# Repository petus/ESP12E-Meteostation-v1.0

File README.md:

# ESP12E-Meteostation-v1.0<br>
Meteostation with ESP12E (NodeMCU) and Si7021 (temperature and humidity sensor)<br>
<br>
PCB is designed in eagle<br>
The platic box is KM-27<br>
<br>
FLASHING: <br>
 1.) Choose NodeMCU v1.0 (ESP12E Module) in Tools -> Board<br>
for NodeMCU board:<br>
 2.) Upload the code<br>
for PCB with ESP12E:<br>
 2.) Press the Reset button and Flash button together and hold it<br>
 3.) Click to Upload the code in Arduino IDE<br>
 4.) In the moment when the console shows <strong>Uploading</strong> leave the Reset button, then the code will be uploaded<br>
<br>
websites: <br>
CZ http://chiptron.petus.cz/articles.php?article_id=93 <br>
EN http://time4ee.com/articles.php?article_id=33 <br>

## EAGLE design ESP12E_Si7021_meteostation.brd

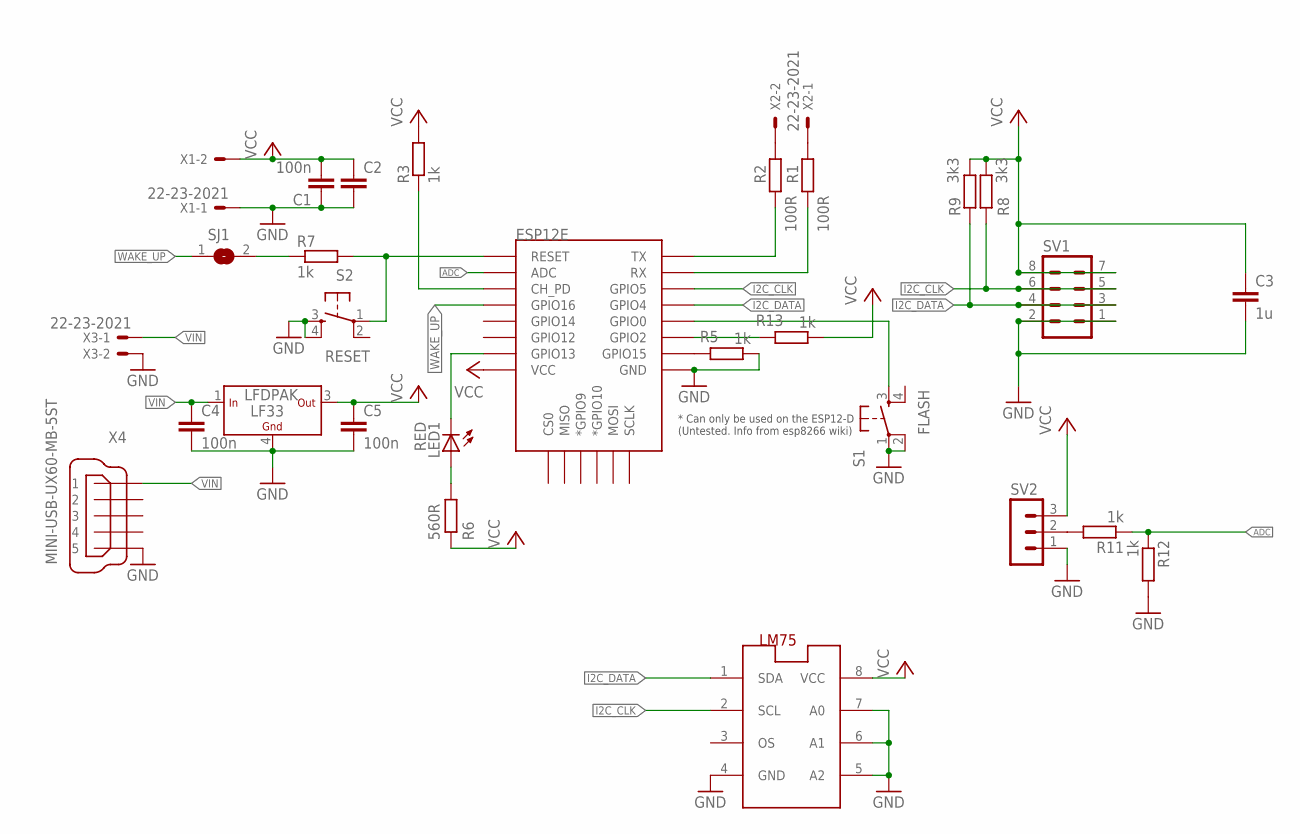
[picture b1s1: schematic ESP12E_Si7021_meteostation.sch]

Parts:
C1: 100n; C3225
C2: C-EUC1206; C1206
C3: 1u; C1206
C4, C5: 100n; C1206
ESP12E: ESP12ESMD; ESP12E-SMD
LED1: RED; CHIPLED_0603
LF33: LFDPAK; DPAK
LM75: LM75_ICN; SO8_LM75
R1, R2: 100R; R0805
R3: 1k; R1206
R5, R7, R13: 1k; R0805
R6: 560R; R0805
R8, R9: 3k3; R0805
R11, R12: 1k; M0805
S1: FLASH; TACTILE-PTH
S2: RESET; TACTILE-PTH
SJ1: SJ
SV1: MA04-2
SV2: MA03-1
X1, X2, X3: 22-23-2021
X4: MINI-USB-UX60-MB-5ST; UX60-MB-5ST

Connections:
ADC: ESP12E.ADC, R11.1, R12.1
GND: C1.1, C2.2, C3.2, C4.2, C5.2, ESP12E.GND, LF33.4 (GND), LM75.4 (GND), LM75.5 (A2), LM75.6 (A1), LM75.7 (A0), R5.1, R12.2, S1.1, S1.2, S2.3, S2.4, SV1.1, SV1.2, SV2.1, X1.1, X3.2, X4.5
I2C_CLK: ESP12E.GPIO5, LM75.2 (SCL), R8.1, SV1.5, SV1.6
I2C_DATA: ESP12E.GPIO4, LM75.1 (SDA), R9.1, SV1.3, SV1.4
unnamed: R1.2, X2.1
unnamed: R2.2, X2.2
unnamed: ESP12E.RXD0 (RX), R1.1
unnamed: ESP12E.TXD0 (TX), R2.1
unnamed: ESP12E.RESET, R7.2, S2.1
unnamed: ESP12E.GPIO15, R5.2
unnamed: ESP12E.CH_PD, R3.1
unnamed: LED1.A, R6.2
unnamed: ESP12E.GPIO13, LED1.C
unnamed: R7.1, SJ1.2
unnamed: ESP12E.GPIO2, R13.2
unnamed: ESP12E.GPIO0, S1.3
unnamed: R11.2, SV2.2
VCC: C1.2, C2.1, C3.1, C5.1, ESP12E.VCC, LF33.3 (OUT), LM75.8 (VCC), R3.2, R6.1, R8.2, R9.2, R13.1, SV1.7, SV1.8, SV2.3, X1.2
VIN: C4.1, LF33.1 (IN), X3.1, X4.1
WAKE_UP: ESP12E.GPIO16, SJ1.1

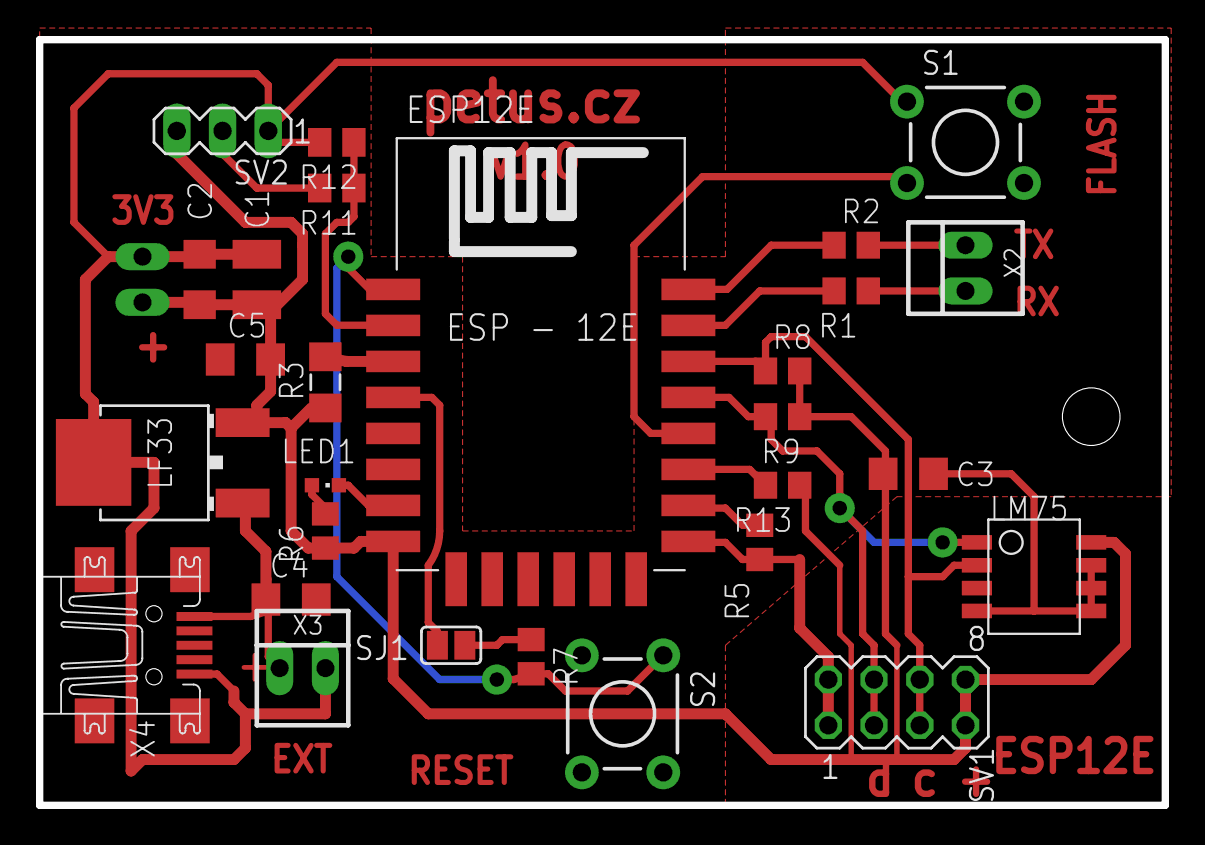
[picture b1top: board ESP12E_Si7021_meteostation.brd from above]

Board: 2 copper layers, 62.5 x 42.5 mm, 29 parts (1 on the bottom side), 20 nets.

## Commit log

2016-10-30 Add files via upload
    schematic
2016-10-30 Add files via upload
    schematic and PCB
2016-11-13 Update ESP12E_Si7021.ino
    bug of minus values
2016-11-13 Update README.md
    description of uploading of code
2017-02-09 Modified calculation between -1 and +1 °C. Added if condition for connection to WiFi
2017-02-18 Update ESP12E_Si7021.ino
    removed the calculation of temperature
    used String instead of calculation
    thanks Arcao (https://plus.google.com/+MartinSloup)

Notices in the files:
parts and their libraries:
Copyright (C) PaJa 2001-2011
SparkFun: Licensing: CC v3.0 Share-Alike You are welcome to use this library for commercial purposes.
